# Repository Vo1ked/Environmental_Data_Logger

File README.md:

# Environmental Data Logger

Автономний реєстратор мікроклімату на ESP32-S3: вимірювання температури, вологості й тиску, локальний архів за 31 календарний день та відновлення роботи після програмних зависань.

**C · ESP-IDF 6.1 · FreeRTOS · SPI · I²C · UART · Light Sleep**

## Можливості

- Вимірювання BME280 та оновлення OLED щосекунди.
- Архівування кожні 30 секунд: поточний день UTC і 30 попередніх, до 89 280 вимірювань за 31 повну добу.
- Циклічна ротація за днями без ручного очищення після заповнення.
- CRC32 записів і заголовків, відновлення індексу після перезапуску.
- Годинник DS1307 із резервним живленням; зберігання UTC та відображення місцевого часу.
- Керування через UART: стан пристрою, читання архіву, налаштування часу й режиму запису.
- Task Watchdog із panic та перезавантаженням; незалежний контроль робочих задач.
- Light Sleep між вимірюваннями з пробудженням за таймером або через UART.

## Архітектура

```mermaid
flowchart LR
    BME[BME280 / SPI] --> Sensor
    RTC[DS1307 / I²C] --> Sensor
    Sensor -->|Вимірювання| Manager
    Manager --> Display --> OLED[SSD1306]
    Manager --> Storage[Flash Writer] --> Archive[Архів за 31 день]
    UART[UART Commands] <--> Manager
    Manager --> WDT[Task Watchdog]
```

| Модуль | Призначення |
| --- | --- |
| `main/sensor` | Вимірювання BME280, читання та встановлення RTC |
| `main/display` | Формування кадру OLED |
| `main/storage` | Добовий кільцевий архів, CRC, збереження та відновлення |
| `main/uart` | Розбір команд та обмін через UART0 |
| `main/manager` | Розклад, стани, маршрутизація повідомлень і сон |
| `main/watchdog` | Перевірка строків виконання операцій та керування TWDT |
| `main/time` | UTC, часовий пояс і часова позначка збірки |

Задачі обмінюються значеннями через черги FreeRTOS. Кожен драйвер має одного власника; спільну шину I²C захищено mutex. Асинхронний logger передає діагностику в системну консоль USB Serial/JTAG. Апаратні адаптери надає бібліотека VolkCoreEmbedded.

## Зберігання даних

Розділ `logdata` займає **1488 КіБ**: 31 слот по 48 КіБ. Слот відповідає календарному дню UTC. Під час першого вимірювання нового дня зберігається буфер попереднього дня та повторно використовується слот, що вийшов за межі вікна зберігання. Пропущені дні не заповнюються штучними даними.

Запис займає 16 байтів і містить UTC timestamp, температуру, вологість, тиск та CRC32. RAM-буфер — **1024 байти, 64 записи**. Повний буфер автоматично зберігається кожні **32 хвилини**. Команда `flush` зберігає лише накопичені записи, тому часті збереження не витрачають вільні залишки секторів. Під час зміни дня буфер також зберігається автоматично.

`read` повертає записи від старих до нових. Індекс `0` відповідає найстарішому доступному запису та змінюється після ротації. Протягом поточної доби глибина архіву становить від 30 до 31 доби. Вимкнення пристрою або недоступність датчика залишають пропуски.

| Область flash | Розмір |
| --- | ---: |
| Завантажувач і службові області | 64 КіБ |
| Застосунок | 448 КіБ |
| Добовий архів | 1488 КіБ |
| Нерозподілений резерв | 48 КіБ |

## Апаратна платформа

ESP32-S3, BME280 із чотирипровідним SPI, DS1307, SSD1306 128×64 та вбудований USB–UART міст плати. Конфігурація flash — 2 МіБ.

| Інтерфейс | GPIO |
| --- | --- |
| I²C SDA / SCL | 8 / 9 |
| SPI MOSI / MISO / SCLK / CS | 11 / 13 / 12 / 10 |
| UART0 TX / RX | 43 / 44 |

Схема підключення й вимоги до рівнів сигналів: [підключення обладнання](docs/wiring_and_uart.md).

## Збирання та запуск

1. Установити ESP-IDF 6.1 та ініціалізувати підмодулі Git: `git submodule update --init --recursive`.
2. У середовищі ESP-IDF вибрати ціль: `idf.py set-target esp32s3`.
3. Перевірити GPIO й часовий пояс у `idf.py menuconfig` → **Environmental Data Logger**.
4. Зібрати проєкт: `idf.py build`.
5. Прошити застосунок і таблицю розділів: `idf.py -p PORT flash monitor`.
6. Відкрити COM-порт вбудованого USB–UART плати (UART0): **115200, 8N1, без керування потоком**, завершення рядка CR, LF або CRLF.
7. Установити актуальний час UTC командою `time set YYYY-MM-DDTHH:MM:SSZ` та перевірити `status`.

**Оновлення розмітки архіву:** потрібні дані слід попередньо вивантажити старою прошивкою. Розташування розділу й розмір добових слотів змінено; попередній архів, зокрема варіант v2 на 744 КіБ, несумісний із новою розміткою. Після прошивання нової таблиці розділів виконати `erase`, а потім `log on`. Очищення видаляє архів; автоматичне перетворення не передбачене.

## Команди

| Команда | Призначення |
| --- | --- |
| `status` | Стан датчиків, архіву, сну, WDT і причина перезапуску |
| `log on` / `log off` | Увімкнення / зупинення накопичення |
| `flush` | Збереження RAM-буфера |
| `read` | Останні 16 збережених записів |
| `read first count` | Читання із заданого індексу; до 256 записів |
| `time set YYYY-MM-DDTHH:MM:SSZ` | Установлення UTC у RTC |
| `erase` | Повне очищення архіву; запис залишається вимкненим |
| `help` | Довідка |

Для пробудження надіслати `UUU` і переведення рядка, дочекатися `READY`, після чого вводити команду. Через 30 секунд без вхідних даних поновлюється періодичний сон. Команди та відповіді виводяться через вбудований USB–UART (UART0). Щосекундний стан, діагностика застосунку, системні логи та panic виводяться через USB Serial/JTAG на другому, прямому USB-роз’ємі. Перед відкриттям іншого термінала закрити monitor, якщо він займає той самий COM-порт.

## Надійність та обмеження

TWDT контролює Manager із таймаутом 5 секунд. Окремі строки контролюють Sensor, Display, UART, підготовку сну та поступ виконання операцій Flash. Помилка пристрою з отриманою відповіддю не вважається зависанням. [Принцип роботи WDT і сценарії перевірки](docs/watchdog.md).

CRC виявляє пошкоджені записи; зайняті байти перерваного запису повторно не програмуються. Ротація звільняє старий день повністю. Втрата живлення під час ротації може видалити цей день до збереження першого запису нового дня. Незбережений RAM-буфер втрачається під час скидання або вимкнення живлення. Перед плановим вимкненням виконати `log off`, потім `flush`.

Переведення RTC назад за останній архівний 30-секундний інтервал зупиняє накопичення, захищаючи хронологію. Повторний запис того самого інтервалу пропускається. Після виправлення часу запис вмикається командою `log on`. Часті апаратні збої можуть вичерпати резерв пошкоджених записів усередині дня. Проєкт не використовує файлову систему й не підтримує шифрування розділу архіву.

## Документація

- [Технічна специфікація](docs/technical_specification.md)
- [Формат архіву та відновлення](docs/storage.md)
- [Підключення й UART](docs/wiring_and_uart.md)
- [Watchdog](docs/watchdog.md)
- [Критерії перевірки](docs/verification.md)

## Ліцензія

Умови використання наведено у [LICENSE](LICENSE).

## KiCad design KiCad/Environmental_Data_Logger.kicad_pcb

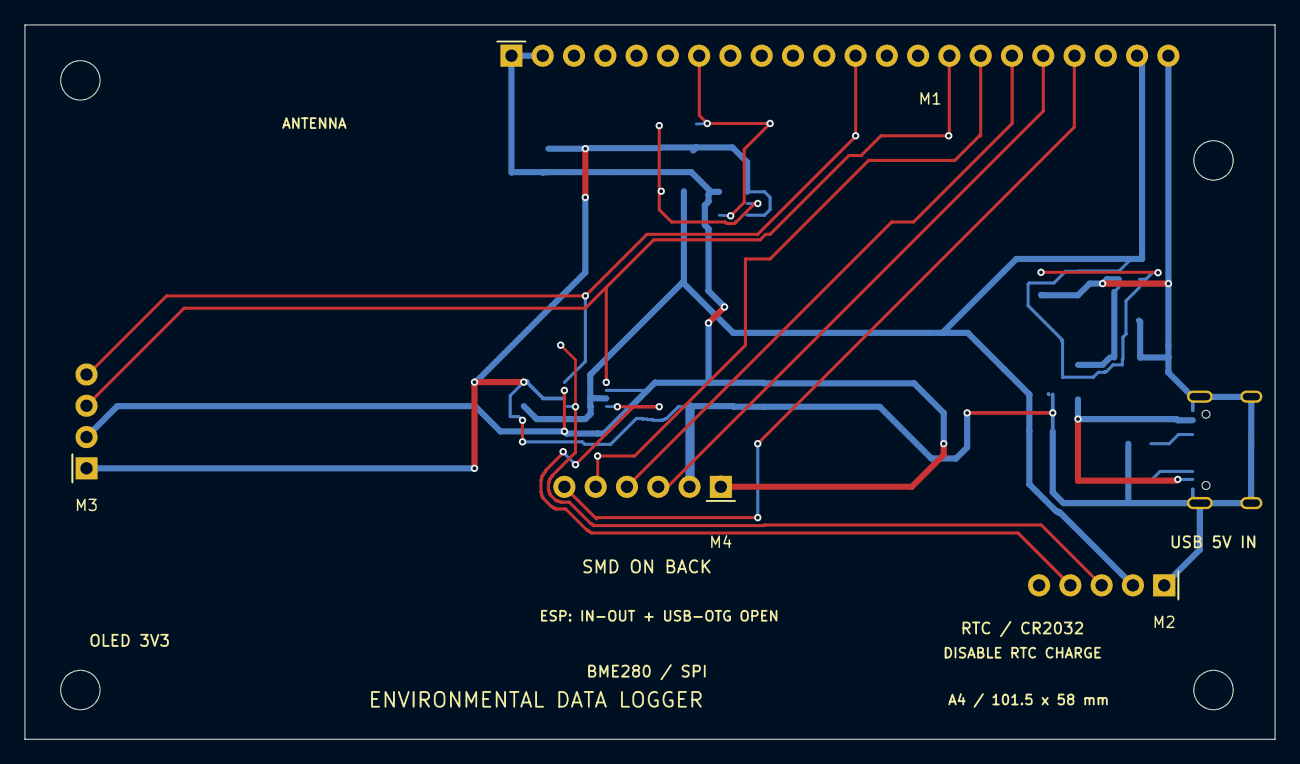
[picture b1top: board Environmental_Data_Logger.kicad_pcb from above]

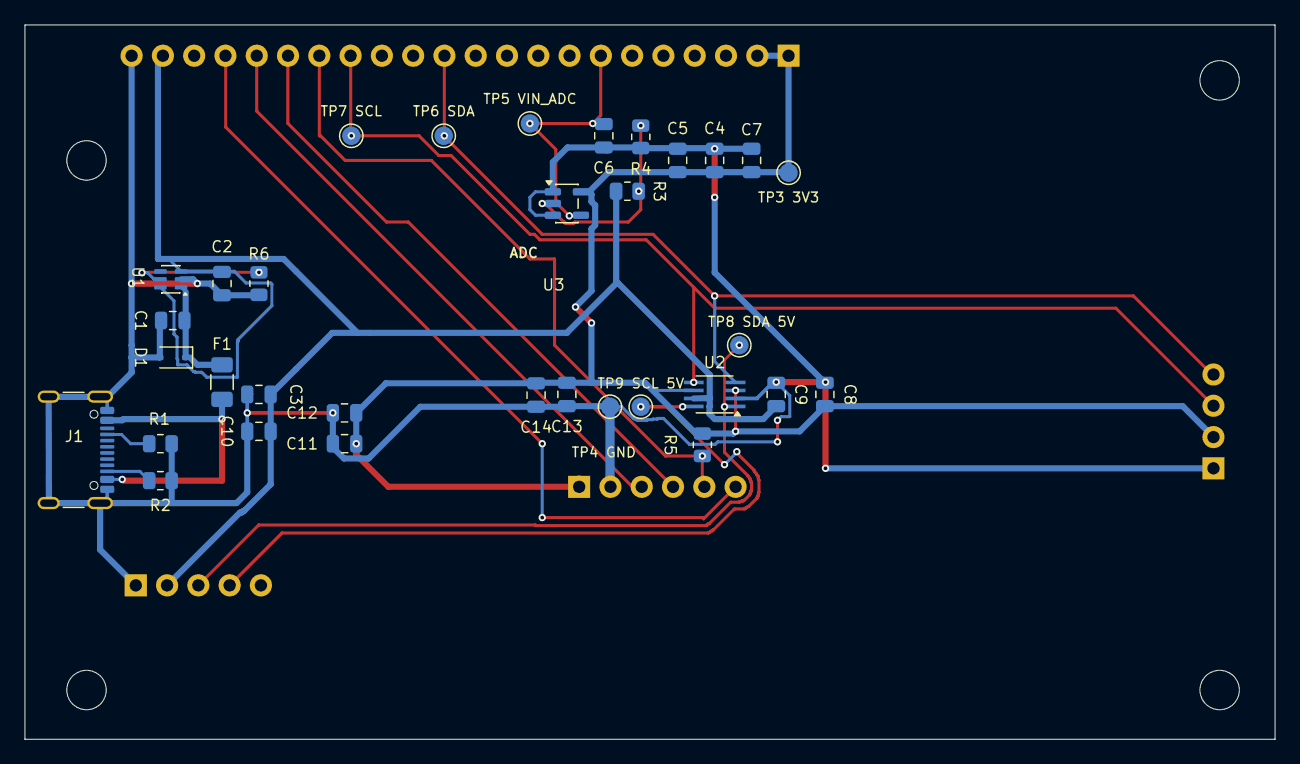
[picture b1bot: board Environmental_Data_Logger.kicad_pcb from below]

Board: 2 copper layers, 101.5 x 58.0 mm, 41 parts (33 on the bottom side), 18 nets.

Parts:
C1: 1u 16V X7R; C_0805_2012Metric
C2: 4.7u 16V X7R; C_0805_2012Metric
C3, C5, C6, C7, C8, C9, C10, C11, C13: 100n 16V X7R; C_0805_2012Metric
C4: 4.7u 10V X7R; C_0805_2012Metric
C12, C14: 1u 10V X7R; C_0805_2012Metric
D1: PESD5V0S1BA; D_SOD-323
F1: 1A fast; Fuse_1206_3216Metric
H1, H2, H3, H4: M3 carrier mounting; MountingHole_3.2mm_M3
J1: USB4105-GF-A; USB_C_Receptacle_GCT_USB4105-xx-A_16P_TopMnt_Horizontal
M1: YD-ESP32-S3; YD_ESP32_S3_LeftRow22
M2: Tiny RTC / DS1307; Tiny_RTC_Row5
M3: SSD1306 128x64; OLED_SSD1306_Row4
M4: GY-BME280 / SPI; BME280_SPI_Row6
R1, R2: 5.1k 1%; R_0805_2012Metric
R3: 27k 1%; R_0805_2012Metric
R4, R5, R6: 10k 1%; R_0805_2012Metric
TP3: +3V3_ESP; TestPoint_Pad_D1.5mm
TP4: GND; TestPoint_Pad_D1.5mm
TP5: VIN_ADC; TestPoint_Pad_D1.5mm
TP6: I2C_SDA; TestPoint_Pad_D1.5mm
TP7: I2C_SCL; TestPoint_Pad_D1.5mm
TP8: RTC_SDA_5V; TestPoint_Pad_D1.5mm
TP9: RTC_SCL_5V; TestPoint_Pad_D1.5mm
U1: LM66100DCKR; SOT-363_SC-70-6
U2: TCA9406DCTR; SSOP-8_2.95x2.8mm_P0.65mm
U3: SN74CBTLV1G125DBVR; SOT-23-5

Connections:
+3V3_ESP: C4.1, C5.1, C7.1, C8.1, C11.1, C12.1, C13.1, C14.1, M1.1, M1.2, M3.2, M4.1, R5.1, TP3.1, U2.3, U2.6, U3.5
+5V_FUSED: C1.1, D1.1, F1.2, U1.1
+5V_SYS: C2.1, C3.1, C9.1, C10.1, M1.21, M2.2, R3.1, U1.3, U1.6, U2.7
+5V_USB: F1.1, J1.A4, J1.A9, J1.B4, J1.B9
BME_CS: M1.16, M4.5, R5.2
CC1: J1.A5, R1.1
CC2: J1.B5, R2.1
GND: C1.2, C2.2, C3.2, C4.2, C5.2, C6.2, C7.2, C8.2, C9.2, C10.2, C11.2, C12.2, C13.2, C14.2, D1.2, J1.A1, J1.A12, J1.B1, J1.B12, J1.SH, M1.22, M2.1, M3.1, M4.2, R1.2, R2.2, R4.2, R6.2, TP4.1, U1.2, U2.2, U3.1, U3.3
I2C_SCL: M1.15, M3.3, TP7.1, U2.5
I2C_SDA: M1.12, M3.4, TP6.1, U2.4
POWER_ST: R6.1, U1.5
RTC_SCL_5V: M2.4, TP9.1, U2.8
RTC_SDA_5V: M2.3, TP8.1, U2.1
SPI_MISO: M1.19, M4.6
SPI_MOSI: M1.17, M4.4
SPI_SCK: M1.18, M4.3
VIN_ADC: C6.1, M1.7, TP5.1, U3.4
VIN_DIV: R3.2, R4.1, U3.2

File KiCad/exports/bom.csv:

Reference,Value,MPN,Footprint,Assembly notes
J1,USB4105-GF-A,USB4105-GF-A,EDL:USB_C_Receptacle_GCT_USB4105-xx-A_16P_TopMnt_Horizontal,
R1,5.1k 1%,0805 5.1k 1%,EDL:R_0805_2012Metric,
R2,5.1k 1%,0805 5.1k 1%,EDL:R_0805_2012Metric,
F1,1A fast,0466001.NR,EDL:Fuse_1206_3216Metric,Verify supplier resistance; test RTC rail >=4.5V under full load
D1,PESD5V0S1BA,PESD5V0S1BA,EDL:D_SOD-323,"ESD protection, not sustained overvoltage protection"
C1,1u 16V X7R,,EDL:C_0805_2012Metric,
U1,LM66100DCKR,LM66100DCKR,EDL:SOT-363_SC-70-6,CE tied to VOUT for reverse-current blocking; NC pin 4 open; unused ST held low via R6
R6,10k 1%,,EDL:R_0805_2012Metric,
C2,4.7u 16V X7R,,EDL:C_0805_2012Metric,
C3,100n 16V X7R,,EDL:C_0805_2012Metric,
M1,YD-ESP32-S3,,EDL:YD_ESP32_S3_LeftRow22,IN-OUT OPEN; USB-OTG OPEN; use onboard CH343P USB for commands
C4,4.7u 10V X7R,,EDL:C_0805_2012Metric,
C5,100n 16V X7R,,EDL:C_0805_2012Metric,
R3,27k 1%,,EDL:R_0805_2012Metric,
R4,10k 1%,,EDL:R_0805_2012Metric,
U3,SN74CBTLV1G125DBVR,SN74CBTLV1G125DBVR,EDL:SOT-23-5,Ioff isolates ADC divider when ESP 3V3 is absent
C6,100n 16V X7R,,EDL:C_0805_2012Metric,
C7,100n 16V X7R,,EDL:C_0805_2012Metric,
TP1,+5V_USB,,EDL:TestPoint_Pad_D1.5mm,
TP2,+5V_SYS,,EDL:TestPoint_Pad_D1.5mm,
TP3,+3V3_ESP,,EDL:TestPoint_Pad_D1.5mm,
TP4,GND,,EDL:TestPoint_Pad_D1.5mm,
TP5,VIN_ADC,,EDL:TestPoint_Pad_D1.5mm,
U2,TCA9406DCTR,TCA9406DCTR,EDL:SSOP-8_2.95x2.8mm_P0.65mm,Partial-power-down isolation; internal 10k pulls on both sides
M2,Tiny RTC / DS1307,,EDL:Tiny_RTC_Row5,CR2032; disable charging path and verify VBAT network before installation
C8,100n 16V X7R,,EDL:C_0805_2012Metric,
C9,100n 16V X7R,,EDL:C_0805_2012Metric,
C10,100n 16V X7R,,EDL:C_0805_2012Metric,
M3,SSD1306 128x64,,EDL:OLED_SSD1306_Row4,Front view: GND VDD SCK SDA; SCK means I2C SCL
C11,100n 16V X7R,,EDL:C_0805_2012Metric,
C12,1u 10V X7R,,EDL:C_0805_2012Metric,
M4,GY-BME280 / SPI,,EDL:BME280_SPI_Row6,Keep away from ESP/regulator heat; inspect sensor ID 0x60
R5,10k 1%,,EDL:R_0805_2012Metric,
C13,100n 16V X7R,,EDL:C_0805_2012Metric,
C14,1u 10V X7R,,EDL:C_0805_2012Metric,
TP6,I2C_SDA,,EDL:TestPoint_Pad_D1.5mm,
TP7,I2C_SCL,,EDL:TestPoint_Pad_D1.5mm,
TP8,RTC_SDA_5V,,EDL:TestPoint_Pad_D1.5mm,
TP9,RTC_SCL_5V,,EDL:TestPoint_Pad_D1.5mm,
